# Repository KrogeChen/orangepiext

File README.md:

# orangepiext
orange pi zero extend board

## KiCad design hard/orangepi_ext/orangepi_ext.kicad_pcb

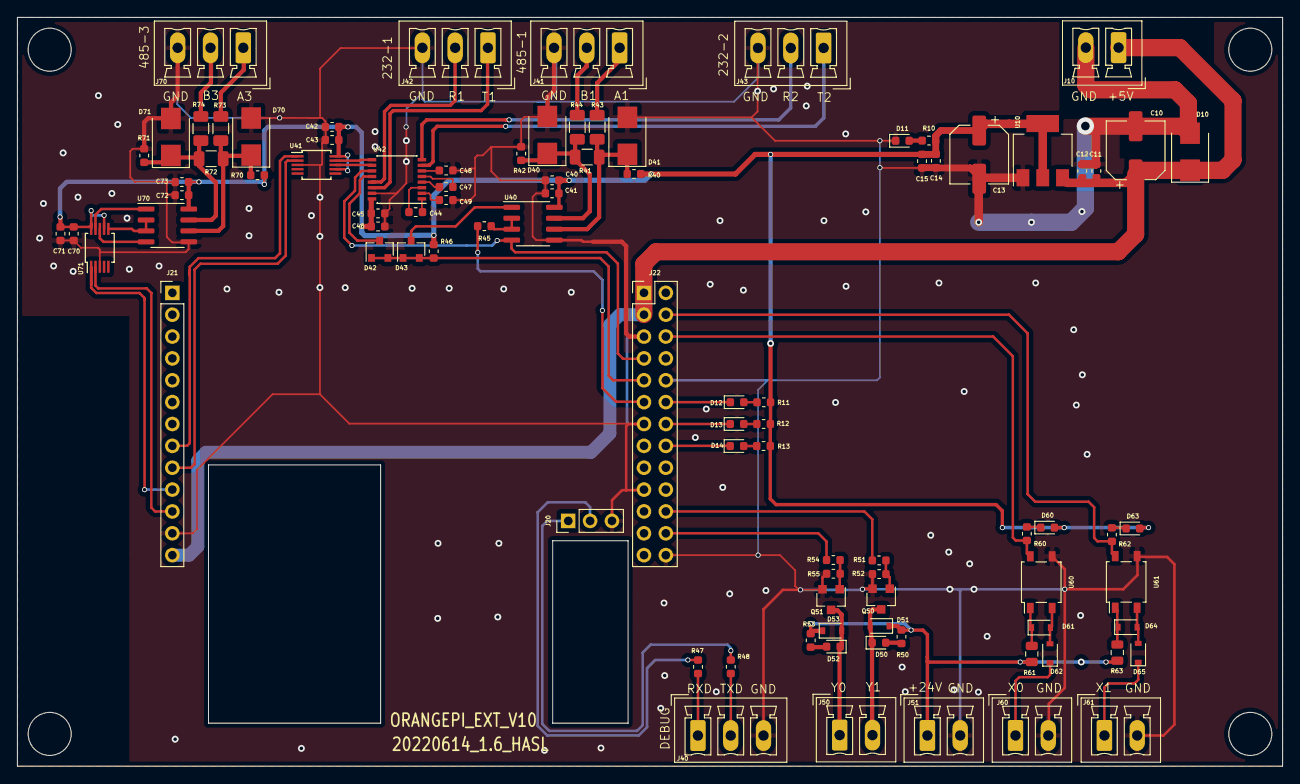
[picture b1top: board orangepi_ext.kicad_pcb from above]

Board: 2 copper layers, 147.0 x 87.0 mm, 92 parts (0 on the bottom side), 66 nets.

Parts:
C10, C13: 220uF; CP_Elec_6.3x5.4
C11, C14, C41, C43, C45, C71, C73: 1uF; C_0603_1608Metric
C12, C15, C40, C42, C44, C46, C47, C48, C49, C70, C72: 100nF; C_0603_1608Metric
D10: SMBJ5.0A; D_SMB
D11, D12, D13, D14, D50, D52, D60, D63: Red; LED_0603_1608Metric
D40, D41, D70, D71: SMBJ12A; D_SMB
D42, D43: BAT54C; SOT-23
D51, D53, D61, D62, D64, D65: 1N4148; D_SOD-323F
J10: Power; PhoenixContact_MCV_1,5_2-G-3.81_1x02_P3.81mm_Vertical
J20: DEBUG; PinHeader_1x03_P2.54mm_Vertical
J21: EXT1; PinHeader_1x13_P2.54mm_Vertical
J22: EXT2; PinHeader_2x13_P2.54mm_Vertical
J40: DBG; PhoenixContact_MCV_1,5_3-G-3.81_1x03_P3.81mm_Vertical
J41: 485-1; PhoenixContact_MCV_1,5_3-G-3.81_1x03_P3.81mm_Vertical
J42: 232-1; PhoenixContact_MCV_1,5_3-G-3.81_1x03_P3.81mm_Vertical
J43: 232-2; PhoenixContact_MCV_1,5_3-G-3.81_1x03_P3.81mm_Vertical
J50: YOUT; PhoenixContact_MCV_1,5_2-G-3.81_1x02_P3.81mm_Vertical
J51: VDD; PhoenixContact_MCV_1,5_2-G-3.81_1x02_P3.81mm_Vertical
J60, J61: XIN; PhoenixContact_MCV_1,5_2-G-3.81_1x02_P3.81mm_Vertical
J70: 485-3; PhoenixContact_MCV_1,5_3-G-3.81_1x03_P3.81mm_Vertical
Q50, Q51: AO3400A; SOT-23_big
R10, R11, R12, R13, R60, R62: 2.7k; R_0603_1608Metric
R40, R42, R46, R52, R55, R70, R71: 10k; R_0603_1608Metric
R41, R72: NP_120; R_1206_3216Metric
R43, R44: 20; R_1206_3216Metric
R45, R47, R48, R51, R54: 33R; R_0603_1608Metric
R50, R53: 33k; R_0603_1608Metric
R61, R63: 7.5k; R_0805_2012Metric
R73, R74: 20R; R_1206_3216Metric
U10: AMS1117-3.3; SOT-223
U40, U70: SP3485EN; SOIC-8_3.9x4.9mm_P1.27mm
U41, U71: CH340E; MSOP-10_3x3mm_P0.5mm
U42: SP3232EEY; SSOP-16_4.4x5.2mm_P0.65mm
U60, U61: EL357N; SO-4_4.4x4.3mm_P2.54mm

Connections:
/DM2: J21.11, U71.2
/DM3: J21.9, U41.2
/DP2: J21.10, U71.1
/DP3: J21.8, U41.1
/PC5: D13.1, J22.14
/PC6: D12.1, J22.12
/PC8: D14.1, J22.16
/PC11: J22.11, R45.2
/PH4: J22.6, R60.2, U60.4
/PH5: J22.4, R62.2, U61.4
/PH6: J22.24, R54.2
/PH8: J22.22, R51.2
/R1_232: J42.2, U42.13
/R2_232: J43.2, U42.8
/R51: D42.3, U42.12
/R52: D43.3, U40.1
/RS1_A: J41.1, R43.1
/RS1_B: J41.2, R44.1
/RS3_A: J70.1, R73.1
/RS3_B: J70.2, R74.1
/RX5: D42.1, D42.2, D43.1, D43.2, J22.9, R46.1
/RXD: J20.2, R47.2
/T1_232: J42.1, U42.14
/T2_232: J43.1, U42.7
/TX5: J22.7, U40.4, U42.11
/TXD: J20.1, R48.2
/UR3: U41.9, U42.9
/UT3: U41.8, U42.10
/V5V: C10.1, C11.1, C12.1, D10.1, J10.1, J21.13, J22.1, J22.3, U10.3
/X0: D62.1, J60.1
/X1: D65.1, J61.1
/Y0: D52.1, D53.2, J50.1, Q51.3
/Y1: D50.1, D51.2, J50.2, Q50.3
GND: C10.2, C11.2, C12.2, C13.2, C14.2, C15.2, C40.2, C41.2, C42.1, C43.1, C45.2, C46.1, C48.2, C49.2, C70.1, C71.1, C72.2, C73.2, D10.2, D11.1, D40.2, D41.2, D70.2, D71.2, J10.2, J20.3, J21.12, J22.5, J22.10, J22.13, J22.19, J22.26, J40.3, J41.3, J42.3, J43.3, J51.2, J60.2, J61.2, J70.3, Q50.2, Q51.2, R42.1, R52.2, R55.2, R71.1, U10.1, U40.5, U41.3, U42.15, U60.3, U61.3, U70.5, U71.3
unnamed: C44.1, U42.1
unnamed: C44.2, U42.3
unnamed: C47.1, U42.4
unnamed: C47.2, U42.5
unnamed: C48.1, U42.6
unnamed: C49.1, U42.2
unnamed: D11.2, R10.1
unnamed: D12.2, R11.1
unnamed: D13.2, R12.1
unnamed: D14.2, R13.1
unnamed: D40.1, R41.1, R42.2, R44.2, U40.7
unnamed: D41.1, R40.1, R41.2, R43.2, U40.6
unnamed: D50.2, R50.1
unnamed: D52.2, R53.1
unnamed: D60.1, R60.1
unnamed: D61.1, R61.1, U60.1
unnamed: D61.2, D62.2, U60.2
unnamed: D63.1, R62.1
unnamed: D64.1, R63.1, U61.1
unnamed: D64.2, D65.2, U61.2
unnamed: D70.1, R70.1, R72.2, R73.2, U70.6
unnamed: D71.1, R71.2, R72.1, R74.2, U70.7
unnamed: J40.1, R47.1
unnamed: J40.2, R48.1
unnamed: Q50.1, R51.1, R52.1
unnamed: Q51.1, R54.1, R55.1
unnamed: R45.1, U40.2, U40.3
unnamed: U70.1, U71.9
unnamed: U70.2, U70.3, U71.6
unnamed: U70.4, U71.8
VCC: C13.1, C14.1, C15.1, C40.1, C41.1, C42.2, C43.2, C45.1, C46.2, C70.2, C71.2, C72.1, C73.1, D60.2, D63.2, R10.2, R11.2, R12.2, R13.2, R40.2, R46.2, R70.2, U10.2, U10.4, U40.8, U41.7, U41.10, U42.16, U70.8, U71.7, U71.10
VDD: D51.1, D53.1, J51.1, R50.2, R53.2, R61.2, R63.2

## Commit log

2022-06-14 orange pi extend hardware designed is finish.
2022-06-15 orange pi extend hardware version 10 is outward processing
2022-12-11 修正后的 schematic
